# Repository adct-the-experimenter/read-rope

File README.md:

# Read Rope 

## Moved to new location https://gitlab.com/pab44/read-rope 

This is an open-source hardware project for a device that outputs a certain voltage depending on where the rope/wire is bent.

Hackaday project: https://hackaday.io/project/166557-read-rope-electronic-nerve

Resistive Flex Sensor used: https://www.adafruit.com/product/1070

# How It Works:

A resistive flex sensor is in parallel with a limiter resistor.

The resistive flex sensor increases in resistance when bent, which increases the voltage at the output.

The limiter resistor in parallel to the resistive flex sensor scales the increase in resistance, which also scales the increase in voltage at the output.

There is a series chain of flexible sections, each containing a parallel combination of a resistive flex sensor and limiter resistor.

Different values for a limiter resistor in each section make for several equivalent resistors in series with each other
that contribute different increases in output voltage when bent depending on the limiter resistor value.

If individual limiter resistors resistance value in each section of the chain were set to make 
the limiter resistor value dependent on the distance from the output node,

then, the increase in output voltage would depend on the distance of a flexible section from the output node
thus making output voltage depend on the location of the bend of a flex resistor due to the limiter resistor's 
value depending on location of the bend.

See the diagram/schematic/figure for read rope circuit in read-rope-flex-resistor-diagram.png 
and the sample results in read-rope-sample-result-4-sections.png.

# Applications:
 - Control for disabled 
 - Virtual Reality/ Augmented Reality (e.g. track precise movement of finger bend, arm bend, leg bend)
 - Interactive control for video games
 - Interactive control for electronic musical instruments
 - Interactive control for training simulation

# Simulation

Have python and ngspice installed.

Run python script read-rope-flex-resistor-circuit-sim.py

    python read-rope-flex-resistor-circuit-sim.py

## Interpreting Output
  
1. Look at the Equivalent Resistance at Output vs Combination graph.
2. Determine the combination of bends you want to see.
 - 0 = no bend, 1 = bend
 - combination 1 = 01 = no bend at section 1, bend at section 0
3. Look up the equivalent resistant value at output for the combination selected in the Equivalent Output Resistance vs Combination graph.
4. Look at the Output Voltage vs Equivalent Resistance at Output graph.
5. Look up the output voltage for equivalent resistance in Output Voltage vs Equivalent Resistance at Output graph.
  
## Interpreting bend combination from output voltage.

1. Look at the Output Voltage vs Equivalent Resistance at Output graph.
2. In Output Voltage vs Equivalent Resistance at Output graph, look up the equivalent resistance for output voltage read.
3. Look at the Equivalent Resistance at Output vs Combination graph.
4. In Equivalent Resistance at Output vs Combination graph, look up the combination number for the equivalent resistant value at output.
5. Determine the combination of bends from the combination number.
	- 0 = no bend, 1 = bend
	- combination 1 = 001 = no bend at section 2,no bend at section 1, bend at section 0
	- combination 4 = 100 = bend at section 2, no bend at section 1, no bend at section 0

## Circuit

VCC-Rtrack-Req-GND
 
Vout = VCC * (Req / (Rtrack + Req))

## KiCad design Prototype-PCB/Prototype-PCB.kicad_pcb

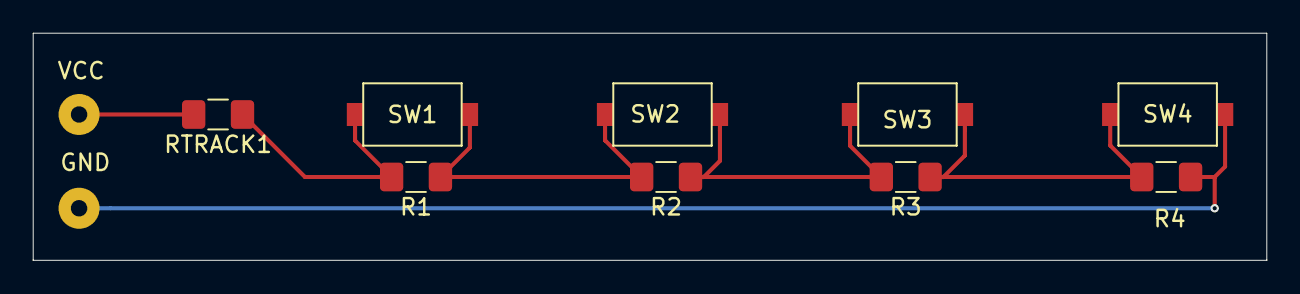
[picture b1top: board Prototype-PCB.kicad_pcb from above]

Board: 2 copper layers, 75.2 x 13.8 mm, 11 parts (0 on the bottom side), 6 nets.

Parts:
GND: SolderWirePad_1x01_Drill1mm
R1: 9k; R_1206_3216Metric_Pad1.42x1.75mm_HandSolder
R2: 7k; R_1206_3216Metric_Pad1.42x1.75mm_HandSolder
R3: 3k; R_1206_3216Metric_Pad1.42x1.75mm_HandSolder
R4: 1k; R_1206_3216Metric_Pad1.42x1.75mm_HandSolder
RTRACK1: 20k; R_1206_3216Metric_Pad1.42x1.75mm_HandSolder
SW1, SW2, SW3, SW4: SW_SPST; KSR221GNCLFS-SMT-NCSPST
VCC: SolderWirePad_1x01_Drill1mm

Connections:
GND: GND.1, R4.1, SW4.2
unnamed: R1.1, R2.2, SW1.2, SW2.1
unnamed: R2.1, R3.2, SW2.2, SW3.1
unnamed: R3.1, R4.2, SW3.2, SW4.1
VCC: RTRACK1.2, VCC.1
vout: R1.2, RTRACK1.1, SW1.1

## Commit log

2019-07-13 Started tracking this project.
2019-07-13 Made a README.md and updated simulations for better interpretation of results.
2019-07-13 Updating README.md
2019-07-13 Updated README.md for better reading.
2019-07-14 Added visual schematic/diagrams to make it easier to understand how the hardware works.
2019-07-14 Licensed the hardware under BSD3 license.
2019-07-14 Fixed mistake in README.md explanation.
2019-07-14 Fixed mistake with diagrams.
2019-07-16 Added images of proof of concept prototype.
2019-07-16 Resized pictures to be smaller for easier reading.
2019-07-20 Added simulation for the 4 bend read rope physical prototype that will be made.
2019-07-23 Updated comments in read-rope-4-bend-prototype-sim.py file
2019-07-23 Made pdf of image showing applications for the read rope.
2019-08-08 Added kicad schematic and kicad project file for flexible pcb design.
2019-08-08 Added results of python simulation in an easy to read picture.
2019-08-15 Started pcb with associated footprints for components.
2019-08-15 Made pcb prototype with vias connecting SMD components on both sides.
2019-08-20 Made some gerber files and put a pad in pcb for ground connection.
2019-09-16 Added LTSpice simulation with load resistor included.
2019-09-16 Added goal for ltspice simulation.
2019-09-16 Modified read-rope-4-bend-prototype to include a load resistor into the calculations.
2019-11-10 Updated ltspice simulation and changed resistor values to get a 10k ohm output impedance to have device be used with microcontroller.
2019-11-10 Updated README.md. Removed python simulation since LTSpice does the same job with ease.
2019-11-10 Removed unneeded python simulation files.
2019-11-10 Removed empty .asc file.
2019-11-17 Modified the pcb file. Changed the footprints for SMT resistors.
2019-11-17 Updated gerber.zip file.
2019-11-17 Fixed a mistake. Added a through-hole pad to connect output.
2019-12-24 Moved files based on older first concepts about how read rope worked to old_base directory.
2019-12-24 Removed copies of files.
2019-12-24 Added a python script to later implement a circuit simulation using ngpsice.
2019-12-24 Added circuit creation and ngspice circuit simulation run to python file.
2019-12-26 Added function to read output of simulation from a file.
2019-12-26 Added use of output for plotting results.
2019-12-26 Added capability to make a read rope with any number of flexible sections as long as limiter resistors are manually defined for each section.
2019-12-26 Added informative comments to the python simulation file.
2019-12-26 Removed results files and added gitignore.
2019-12-26 Updated README.md to include flex sensor explanation.
2019-12-26 Updated README.md for interpreting output.
2019-12-27 Put in a comment to state good combos for different number of sections.
2019-12-27 Added circuit diagram for use of resistive flex sensor.
2019-12-27 Changed bend and flat resistance values of resisitive flex sensor to reflect actual sensor.
2019-12-28 Added picture of sample results.
2020-01-01 Replaced picture of result with one reflecting 4 sections.
2020-01-03 Made track resistor which is the resistor between power supply and output of volt divider variable.
2020-01-03 Changed order of plots shown.
2020-01-03 Added plot that shows output voltage vs combination bend.
2020-01-03 Made source voltage vcc variable.
2020-01-03 Replaced picture of sample results.
2020-01-04 Added arduino ADC code. Included hackaday project link.
2020-01-04 Changed pictures and diagram to match current 3 section prototype made.
2020-01-04 Added picture for prototype version 1.3 of read rope.
2020-01-07 Changed pictures.
2020-01-16 Updated README.md. Fixed broken links to pictures.
2020-01-24 Programmed arduino to calibrate and read bends based on UART serial communications.
2020-04-13 Added some code for a library to abstract reading from read rope device.
2020-04-16 Added CMakeLists.txt and subdirectories for building library.
2020-04-16 Fixed CMakeLists.txt errors.
2020-04-16 Fixed compilation errors.
2020-04-16 Added instructions for installing the library.
2020-04-16 Added some code for a test program to test the library functions.
2020-04-16 Added gitignore in test directory.
2020-04-16 Removed files.
2020-04-18 Fixedadc code compile errors.
2020-04-18 Made comments in Arduino ADC code.
2020-04-19 Changed firmware in Arduino prototype. Removed calibration and state machine code to only have read rope device send ADC value.
2020-04-19 Changed arduino firmware. Added more to library.
2020-04-19 Removed build files.
2020-04-19 Completed linux UART USB serial communication in library.
2020-04-19 Added functions to initialize and close system.
2020-04-19 Implemented initialization and close in test.
2020-04-19 Added calibration functionality to the board.
2020-04-19 Added more comments to the library.
2020-04-19 Implemented calibration in test. Changed calibration method.
